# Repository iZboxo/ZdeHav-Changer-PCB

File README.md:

# ZdeHavCANdesignTCHG

> **Klipper CAN toolhead board — STM32G0B1CBT6 + TMC2209**

Custom toolhead board design for Klipper-based 3D printers. The board communicates over CAN bus and is designed for direct mounting on the print head (toolchanger or standard mount).

---

## Photos

<table>
  <tr>
    <td></td>
    <td></td>
    <td></td>
  </tr>
</table>

---

## Overview

https://izboxo.github.io/ZdeHav-Changer-PCB/bom/ibom.html

| Parameter | Value |
|---|---|
| MCU | STM32G0B1CBT6 (Cortex-M0+, 64 MHz, 128 KB Flash, LQFP-48) |
| CAN transceiver | SN65HVD230 (3.3 V, 1 Mbit/s, SOIC-8) |
| Stepper driver | TMC2209 (UART) |
| USB | USB-C (D+ / D−, DFU support) |
| Power input | 5 V via USB-C |
| Logic voltage | 3.3 V |
| Crystal | 16 MHz / 10 pF (HSE) |
| PCB | 4-layer |
| Schematic rev. | 1.0 (2026-02-02) |
| Firmware | Klipper (CANBUS UUID) |

---

## Features

- **CAN bus** — SN65HVD230, 120 Ω termination resistor (R26), slope-control resistor on RS pin
- **TMC2209** — STEP / DIR / EN / DIAG, UART via USART2 (`USART2_TX_2209_PDN`), SpreadCycle/StealthChop
- **Thermistors** — 3× ADC inputs (THERM-1, THERM-2, THERM-3)
- **Heater** — PWM output (`TIM3_HE`) for hotend heater
- **Fan** — PWM output (`TIM3_FAN`) for part cooling fan
- **NeoPixel** — 1× WS2812B-Mini (5 V), GPIO output `GPIO_NEOPIXEL`
- **Piezo buzzer** — GPIO output `GPIO_PIEZO` via dedicated subsheet
- **SWD** — SWDIO / SWCLK for debug (Black Magic Probe / J-Link)
- **BOOT0** — SPDT switch (SW1) for toggling DFU / normal boot
- **Filtered VREF** — ferrite bead (FB1) + bypass capacitor array (C1–C8) for clean analog VREF

---

## Schematic Structure

| Sheet | File | Contents |
|---|---|---|
| Main | `ZdeHavCANdesignTCHG.kicad_sch` | MCU, CAN transceiver, crystal, NeoPixel, SWD, BOOT0 |
| Power | `usbc.kicad_sch` | USB-C connector, 5 V / 3.3 V power, CAN input |
| Piezo | `piezo.kicad_sch` | Piezo buzzer and driver |
| Extruder | `extruder.kicad_sch` | TMC2209, extruder connector |
| TH+HT | `thermistorsandheaters.kicad_sch` | Thermistors (3×), heater, fan MOSFETs |

---

## Pinout MCU (key functions)

| STM32 Pin | Function |
|---|---|
| PD0 | FDCAN1_RX |
| PD1 | FDCAN1_TX |
| PA0 / PA1 | ADC1_IN0 / ADC1_IN1 (THERM-1, THERM-2) |
| PC6 | TIM3_CH1 — heater PWM |
| PC7 | TIM3_CH2 — fan PWM |
| PA13 / PA14 | SWDIO / SWCLK (SWD) |
| PA14 / BOOT0 | BOOT0 (switch SW1) |
| PF0 / PF1 | HSE IN / OUT (16 MHz crystal) |

> See schematic for full pin mapping.

---

## Firmware — Klipper

The board is intended to run as a Klipper CAN node.

Example `printer.cfg` snippet:

```ini
[mcu head0]
canbus_uuid: <YOUR_UUID_HERE>

[extruder]
step_pin: head0:PD1
dir_pin: head0:PD0
# ... fill in remaining pins per your wiring

[temperature_sensor toolhead_NTC]
sensor_type: NTC 100K MGB18-104F39050L32
sensor_pin: head0:PA0
```

---

## Manufacturing

A ready-to-order fabrication archive **`CANTCHG28.zip`** is available in the project files. This file is specifically prepared for **JLCPCB** (4-layer stackup) and contains all necessary files (Gerber, BOM, CPL) for production.

---
## Dependencies

- [KiCad 9.0](https://www.kicad.org/)
- [Klipper firmware](https://github.com/Klipper3d/klipper)

---

## License

This hardware design is released as open-source under the **MIT** license.

---

*Design: Zdeněk Havlát — [zdehav.cz](https://zdehav.cz)*

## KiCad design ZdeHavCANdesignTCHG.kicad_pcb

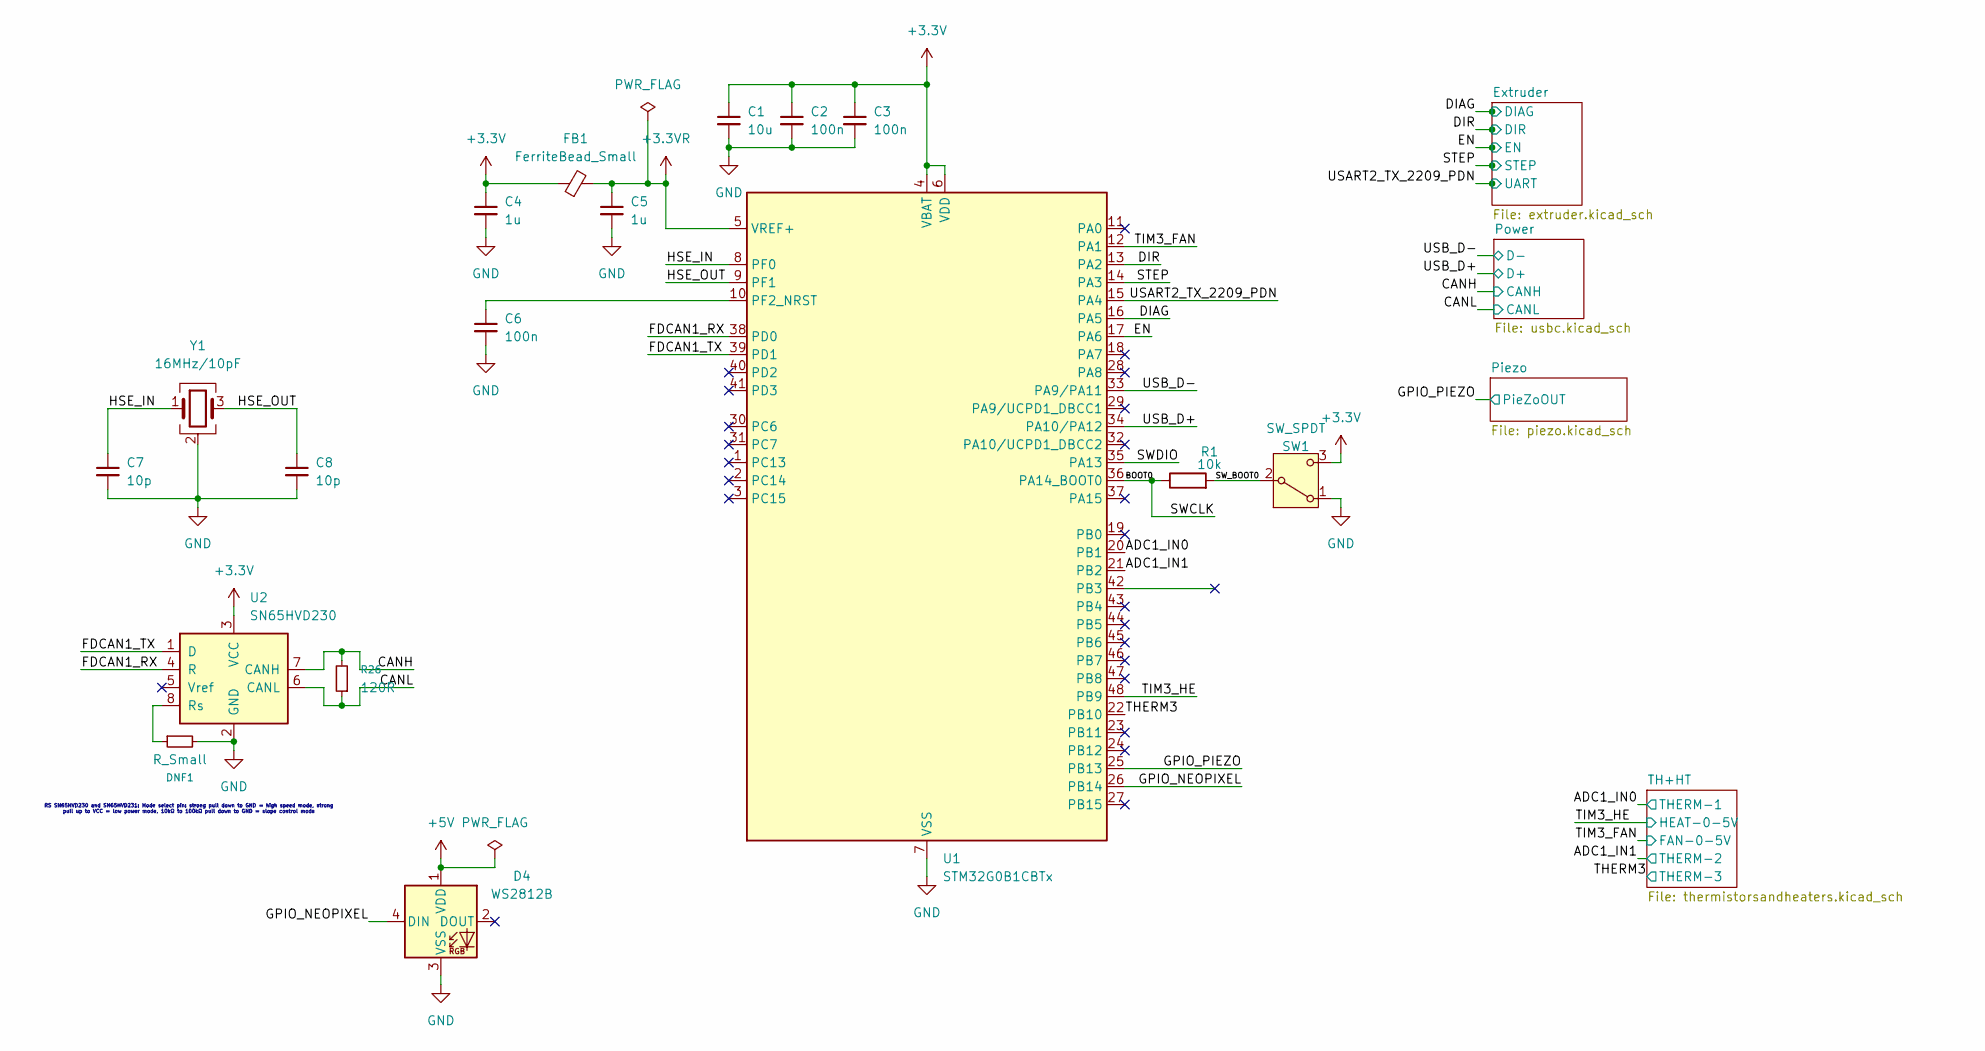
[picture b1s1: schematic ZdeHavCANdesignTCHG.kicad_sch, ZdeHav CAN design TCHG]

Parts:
C1: 10u; C_0603_1608Metric_Pad1.08x0.95mm_HandSolder
C2, C3, C6: 100n; C_0603_1608Metric_Pad1.08x0.95mm_HandSolder
C4, C5: 1u; C_0603_1608Metric_Pad1.08x0.95mm_HandSolder
C7, C8: 10p; C_0603_1608Metric_Pad1.08x0.95mm_HandSolder
D4: WS2812B; LED_WS2812B-Mini_PLCC4_3.5x3.5mm
DNF1: R_Small; R_0603_1608Metric_Pad0.98x0.95mm_HandSolder
FB1: FerriteBead_Small; L_0603_1608Metric_Pad1.05x0.95mm_HandSolder
R1: 10k; R_0603_1608Metric_Pad0.98x0.95mm_HandSolder
R26: 120R; R_0603_1608Metric_Pad0.98x0.95mm_HandSolder
SW1: SW_SPDT; PinHeader_1x03_P1.00mm_Vertical
U1: STM32G0B1CBTx; LQFP-48_7x7mm_P0.5mm
U2: SN65HVD230; SOIC-8_3.9x4.9mm_P1.27mm
Y1: 16MHz/10pF; LFXTAL071255CUTT

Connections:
+3.3V: C1.1, C2.1, C3.1, C4.1, FB1.1, SW1.3 (C), U1.4 (VBAT), U1.6 (VDD), U2.3 (VCC); also elsewhere on the board
+3.3VR: C5.1, FB1.2, U1.5 (VREF+)
+5V: D4.1 (VDD); also elsewhere on the board
/ADC1_IN0: U1.20 (PB1); also elsewhere on the board
/ADC1_IN1: U1.21 (PB2); also elsewhere on the board
/BOOT0: R1.1, U1.36 (PA14_BOOT0)
/CANH: R26.2, U2.7 (CANH); also elsewhere on the board
/CANL: R26.1, U2.6 (CANL); also elsewhere on the board
/DIAG: U1.16 (PA5); also elsewhere on the board
/DIR: U1.13 (PA2); also elsewhere on the board
/EN: U1.17 (PA6); also elsewhere on the board
/FDCAN1_RX: U1.38 (PD0), U2.4 (R)
/FDCAN1_TX: U1.39 (PD1), U2.1 (D)
/GPIO_NEOPIXEL: D4.4 (DIN), U1.26 (PB14)
/GPIO_PIEZO: U1.25 (PB13); also elsewhere on the board
/HSE_IN: C7.1, U1.8 (PF0), Y1.1
/HSE_OUT: C8.1, U1.9 (PF1), Y1.3
/STEP: U1.14 (PA3); also elsewhere on the board
/SWDIO: U1.35 (PA13)
/SW_BOOT0: R1.2, SW1.2 (B)
/THERM3: U1.22 (PB10); also elsewhere on the board
/TIM3_FAN: U1.12 (PA1); also elsewhere on the board
/TIM3_HE: U1.48 (PB9); also elsewhere on the board
/USART2_TX_2209_PDN: U1.15 (PA4); also elsewhere on the board
/USB_D+: U1.34 (PA10/PA12); also elsewhere on the board
/USB_D-: U1.33 (PA9/PA11); also elsewhere on the board
GND: C1.2, C2.2, C3.2, C4.2, C5.2, C6.2, C7.2, C8.2, D4.3 (VSS), DNF1.2, SW1.1 (A), U1.7 (VSS), U2.2 (GND), Y1.2 (G), Y1.4 (G); also elsewhere on the board
unnamed: C6.1, U1.10 (PF2_NRST)
unnamed: DNF1.1, U2.8 (Rs)

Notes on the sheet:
RS SN65HVD230 and SN65HVD231: Mode select pin: strong pull down to GND = high speed mode, strong pull up to VCC = low power mode, 10kΩ to 100kΩ pull down to GND = slope control mode

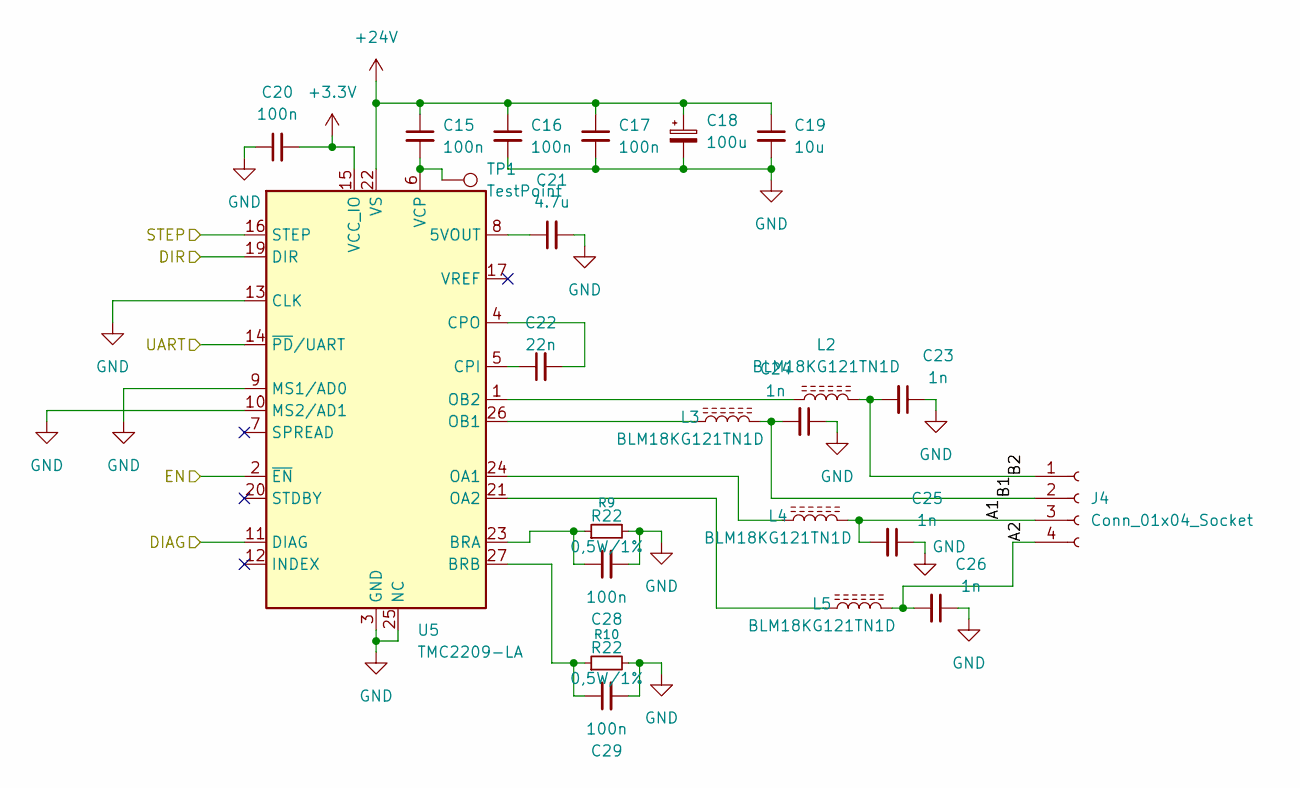
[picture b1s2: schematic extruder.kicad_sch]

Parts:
C15, C16, C17, C20, C28, C29: 100n; C_0603_1608Metric_Pad1.08x0.95mm_HandSolder
C18: 100u; C_Elec_6.3x7.7
C19: 10u; C_1206_3216Metric_Pad1.33x1.80mm_HandSolder
C21: 4.7u; C_0603_1608Metric_Pad1.08x0.95mm_HandSolder
C22: 22n; C_0603_1608Metric_Pad1.08x0.95mm_HandSolder
C23, C24, C25, C26: 1n; C_0603_1608Metric_Pad1.08x0.95mm_HandSolder
J4: Conn_01x04_Socket; JST_XH_B4B-XH-A_1x04_P2.50mm_Vertical
L2, L3, L4, L5: BLM18KG121TN1D; L_0603_1608Metric_Pad1.05x0.95mm_HandSolder
R9, R10: R22; R_1206_3216Metric_Pad1.30x1.75mm_HandSolder
TP1: TestPoint; TestPoint_Pad_D1.0mm
U5: TMC2209-LA; VQFN-28-1EP_5x5mm_P0.5mm_EP3.7x3.7mm_ThermalVias

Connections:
+3.3V: C20.2, U5.15 (VCC_IO); also elsewhere on the board
+24V: C15.1, C16.1, C17.1, C18.1, C19.1, U5.22 (VS), U5.28 (VS); also elsewhere on the board
/DIAG: U5.11 (DIAG); also elsewhere on the board
/DIR: U5.19 (DIR); also elsewhere on the board
/EN: U5.2 (~EN); also elsewhere on the board
/Extruder/A1: C25.2, J4.3, L4.2
/Extruder/A2: C26.2, J4.4, L5.2
/Extruder/B1: C24.2, J4.2, L3.2
/Extruder/B2: C23.2, J4.1, L2.2
/STEP: U5.16 (STEP); also elsewhere on the board
/USART2_TX_2209_PDN: U5.14 (~PD/UART); also elsewhere on the board
GND: C16.2, C17.2, C18.2, C19.2, C20.1, C21.2, C23.1, C24.1, C25.1, C26.1, C28.2, C29.2, R9.2, R10.2, U5.3 (GND), U5.9 (MS1/AD0), U5.10 (MS2/AD1), U5.13 (CLK), U5.18 (GND), U5.25 (NC), U5.29 (GND); also elsewhere on the board
unnamed: C21.1, U5.8 (5VOUT)
unnamed: C28.1, R9.1, U5.23 (BRA)
unnamed: C29.1, R10.1, U5.27 (BRB)
unnamed: C22.1, U5.5 (CPI)
unnamed: C22.2, U5.4 (CPO)
unnamed: L4.1, U5.24 (OA1)
unnamed: L5.1, U5.21 (OA2)
unnamed: L3.1, U5.26 (OB1)
unnamed: L2.1, U5.1 (OB2)
unnamed: C15.2, TP1.1, U5.6 (VCP)

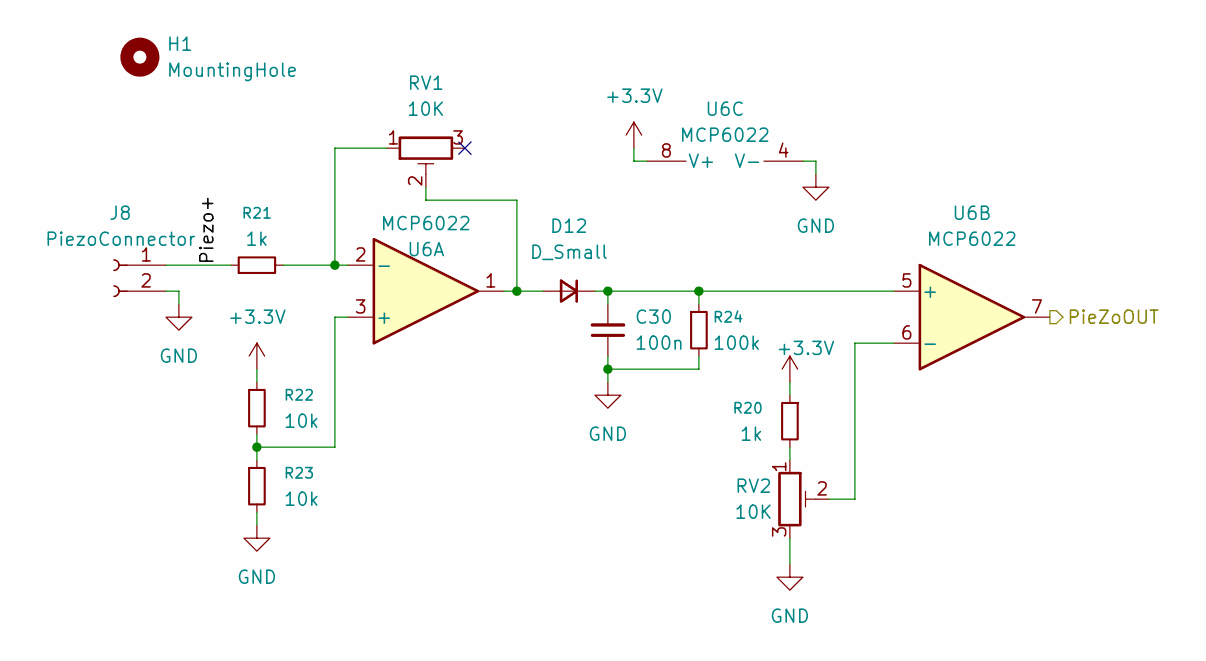
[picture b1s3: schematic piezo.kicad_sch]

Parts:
C30: 100n; C_0603_1608Metric_Pad1.08x0.95mm_HandSolder
D12: D_Small; D_0603_1608Metric_Pad1.05x0.95mm_HandSolder
H1: MountingHole; MountingHole_2.2mm_M2_Pad_Via
J8: PiezoConnector; JST_XH_B2B-XH-A_1x02_P2.50mm_Vertical
R20, R21: 1k; R_0603_1608Metric_Pad0.98x0.95mm_HandSolder
R22, R23: 10k; R_0603_1608Metric_Pad0.98x0.95mm_HandSolder
R24: 100k; R_0603_1608Metric_Pad0.98x0.95mm_HandSolder
RV1, RV2: 10K; Trimmer 10k 3305SMD
U6: MCP6022; TSSOP-8_4.4x3mm_P0.65mm

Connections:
+3.3V: R20.1, R22.1, U6.8 (V+); also elsewhere on the board
/GPIO_PIEZO: U6.7; also elsewhere on the board
/Piezo/Piezo+: J8.1, R21.1
GND: C30.1, J8.2, R23.2, R24.2, RV2.3, U6.4 (V-); also elsewhere on the board
unnamed: D12.2 (A), RV1.2, U6.1
unnamed: C30.2, D12.1 (K), R24.1, U6.5 (+)
unnamed: R20.2, RV2.1
unnamed: R22.2, R23.1, U6.3 (+)
unnamed: R21.2, RV1.1, U6.2 (-)
unnamed: RV2.2, U6.6 (-)

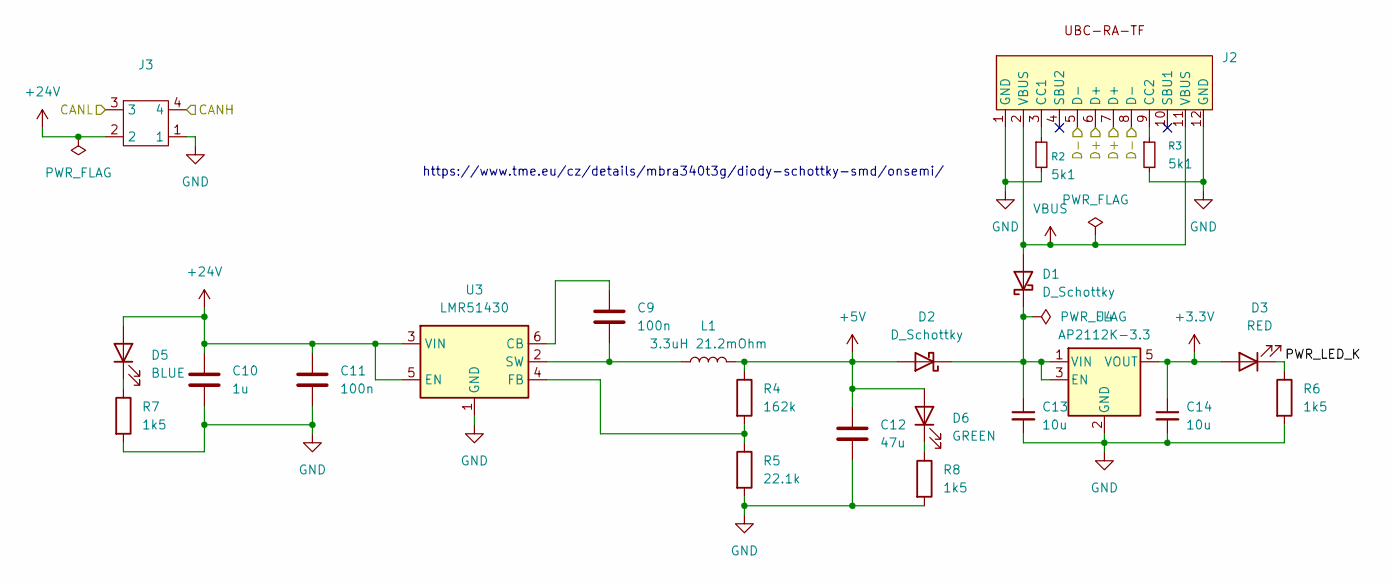
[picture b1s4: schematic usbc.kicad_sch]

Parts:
C9, C11: 100n; C_0603_1608Metric_Pad1.08x0.95mm_HandSolder
C10: 1u; C_0603_1608Metric_Pad1.08x0.95mm_HandSolder
C12: 47u; C_0603_1608Metric_Pad1.08x0.95mm_HandSolder
C13, C14: 10u; C_0603_1608Metric_Pad1.08x0.95mm_HandSolder
D1, D2: D_Schottky; D_SOD-323_HandSoldering
D3: RED; LED_0603_1608Metric_Pad1.05x0.95mm_HandSolder
D5: BLUE; LED_0603_1608Metric_Pad1.05x0.95mm_HandSolder
D6: GREEN; LED_0603_1608Metric_Pad1.05x0.95mm_HandSolder
J2: USBC
J3: Molex Micro-Fit 3.0 4
L1: 3.3uH 21.2mOhm; SD53
R2, R3: 5k1; R_0603_1608Metric_Pad0.98x0.95mm_HandSolder
R4: 162k; R_0603_1608Metric_Pad0.98x0.95mm_HandSolder
R5: 22.1k; R_0603_1608Metric_Pad0.98x0.95mm_HandSolder
R6, R7, R8: 1k5; R_0603_1608Metric_Pad0.98x0.95mm_HandSolder
U3: LMR51430; SOT-23-6
U4: AP2112K-3.3; SOT-23-5

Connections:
+3.3V: C14.1, D3.2 (A), U4.5 (VOUT); also elsewhere on the board
+5V: C12.1, D2.2 (A), D6.2 (A), L1.2, R4.1; also elsewhere on the board
+24V: C10.1, C11.1, D5.2 (A), J3.2, U3.3 (VIN), U3.5 (EN); also elsewhere on the board
/CANH: J3.4; also elsewhere on the board
/CANL: J3.3; also elsewhere on the board
/Power/PWR_LED_K: D3.1 (K), R6.1
/USB_D+: J2.6 (D+), J2.7 (D+); also elsewhere on the board
/USB_D-: J2.5 (D-), J2.8 (D-); also elsewhere on the board
GND: C10.2, C11.2, C12.2, C13.2, C14.2, J2.1 (GND), J2.12 (GND), J3.1, R2.2, R3.2, R5.2, R6.2, R7.2, R8.2, U3.1 (GND), U4.2 (GND); also elsewhere on the board
unnamed: C13.1, D1.1 (K), D2.1 (K), U4.1 (VIN), U4.3 (EN)
unnamed: D5.1 (K), R7.1
unnamed: D6.1 (K), R8.1
unnamed: J2.3 (CC1), R2.1
unnamed: J2.9 (CC2), R3.1
unnamed: C9.2, U3.6 (CB)
unnamed: R4.2, R5.1, U3.4 (FB)
unnamed: C9.1, L1.1, U3.2 (SW)
VBUS: D1.2 (A), J2.2 (VBUS), J2.11 (VBUS)

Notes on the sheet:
https://www.tme.eu/cz/details/mbra340t3g/diody-schottky-smd/onsemi/

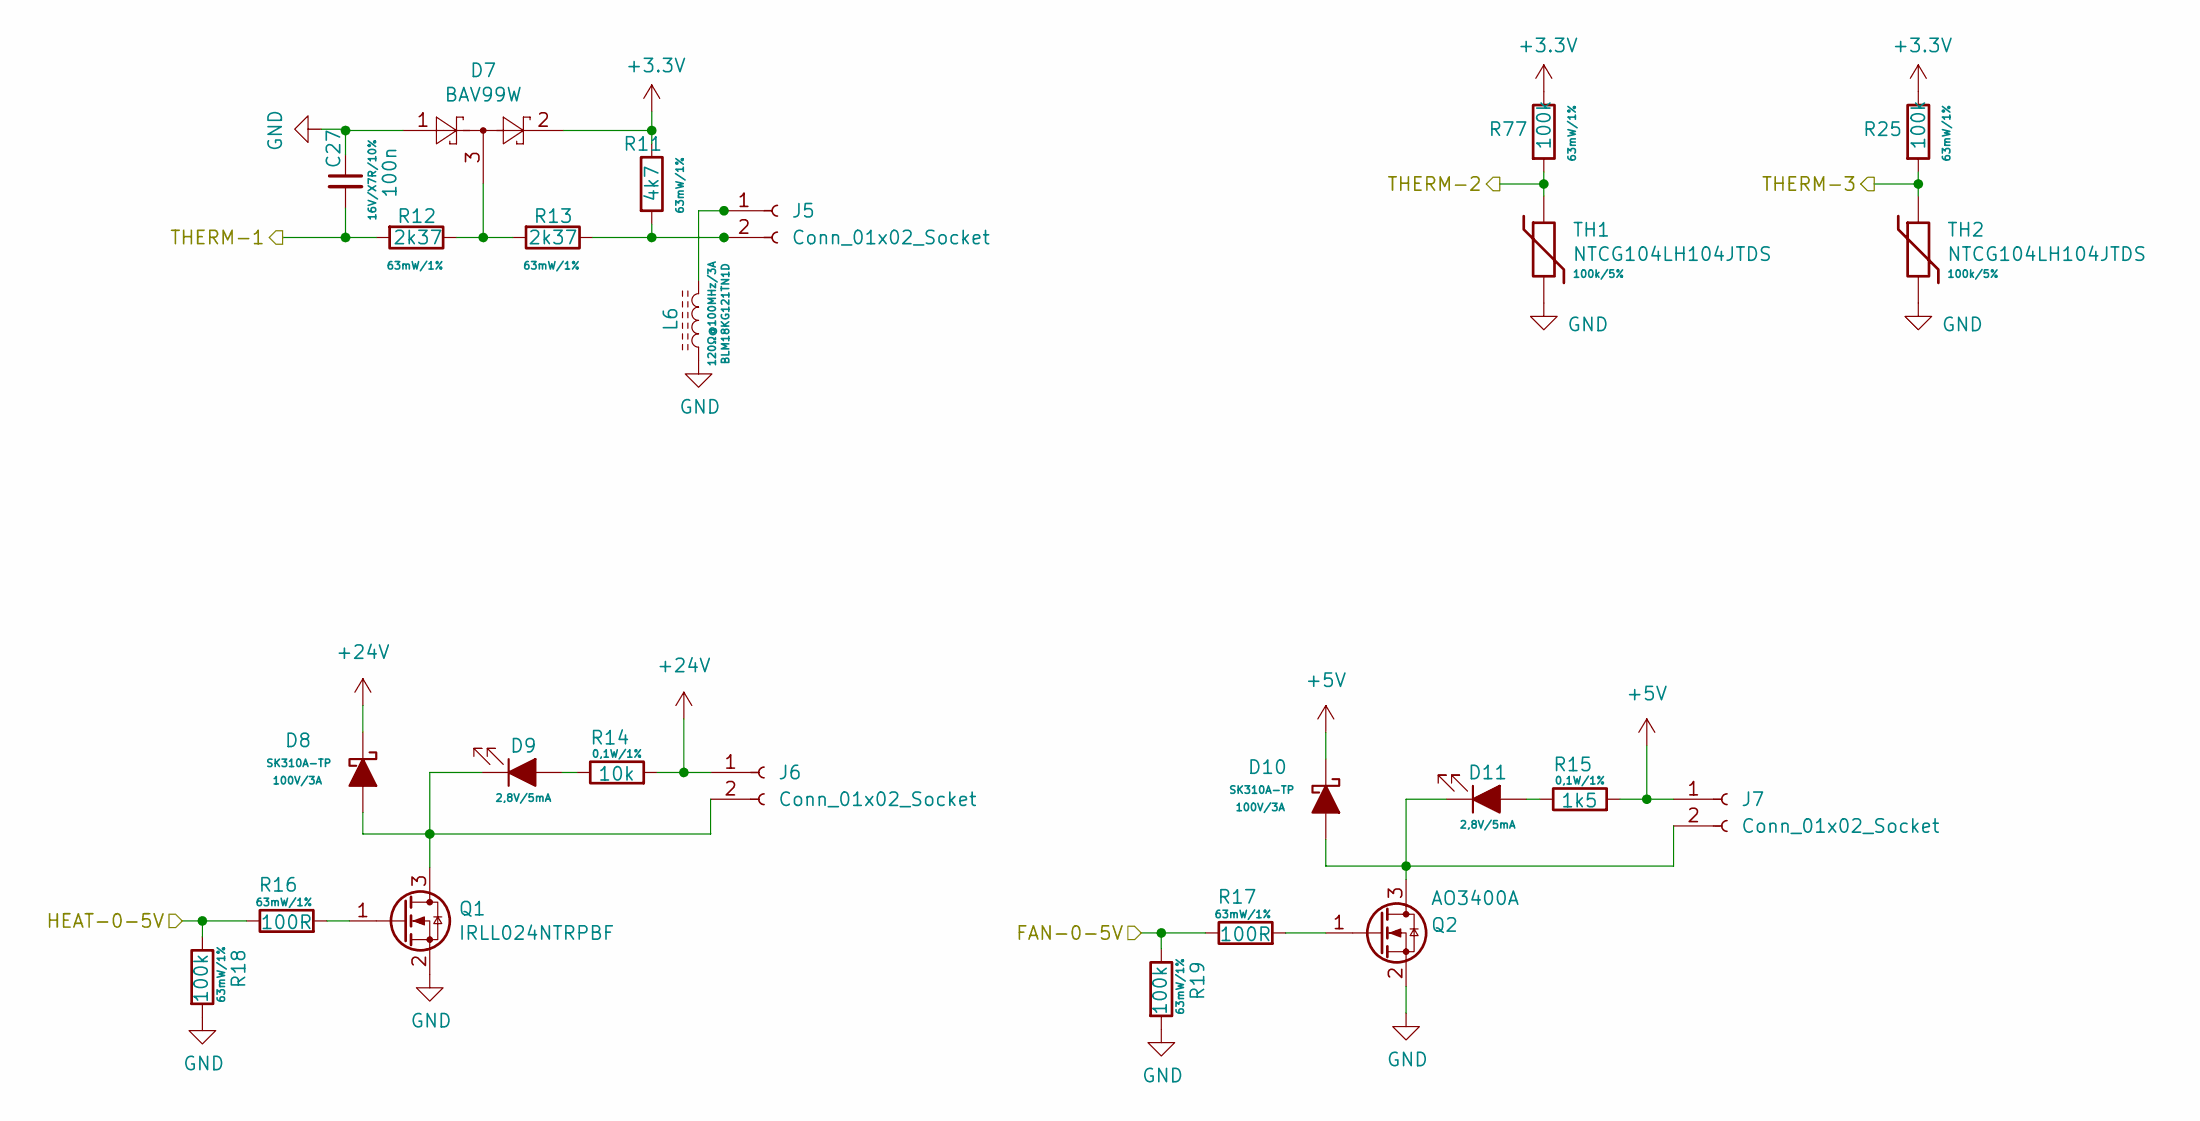
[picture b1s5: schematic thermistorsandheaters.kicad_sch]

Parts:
C27: 100n; C_0603_1608Metric_Pad1.08x0.95mm_HandSolder
D7: BAV99W; SOT-323_SC-70
D8: SK310A-TP; D_SMA
D9, D11: GRN; LED_0603_1608Metric_Pad1.05x0.95mm_HandSolder
D10: SK310A-TP; D_SOD-323_HandSoldering
J5, J6, J7: Conn_01x02_Socket; JST_XH_B2B-XH-A_1x02_P2.50mm_Vertical
L6: BLM18KG121TN1D; L_0603_1608Metric_Pad1.05x0.95mm_HandSolder
Q1: IRLL024NTRPBF; SOT-223-3_TabPin2
Q2: AO3400A; SOT-23
R11: 4k7; R_0603_1608Metric_Pad0.98x0.95mm_HandSolder
R12, R13: 2k37; R_0603_1608Metric_Pad0.98x0.95mm_HandSolder
R14: 10k; R_0603_1608Metric_Pad0.98x0.95mm_HandSolder
R15: 1k5; R_0603_1608Metric_Pad0.98x0.95mm_HandSolder
R16, R17: 100R; R_0603_1608Metric_Pad0.98x0.95mm_HandSolder
R18, R19, R25, R77: 100k; R_0603_1608Metric_Pad0.98x0.95mm_HandSolder
TH1, TH2: NTCG104LH104JTDS; R_0603_1608Metric_Pad0.98x0.95mm_HandSolder

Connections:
+3.3V: D7.2, R11.1, R25.1, R77.1; also elsewhere on the board
+5V: D10.1 (K), J7.1, R15.2; also elsewhere on the board
+24V: D8.1 (K), J6.1, R14.2; also elsewhere on the board
/ADC1_IN0: C27.2, R12.2; also elsewhere on the board
/ADC1_IN1: R77.2, TH1.1; also elsewhere on the board
/THERM3: R25.2, TH2.1; also elsewhere on the board
/TIM3_FAN: R17.1, R19.1; also elsewhere on the board
/TIM3_HE: R16.1, R18.1; also elsewhere on the board
GND: C27.1, D7.1, L6.1, Q1.2 (S), Q2.2 (S), R18.2, R19.2, TH1.2, TH2.2; also elsewhere on the board
unnamed: D7.3, R12.1, R13.2
unnamed: D8.2 (A), D9.1 (K), J6.2, Q1.3 (D)
unnamed: D9.2 (A), R14.1
unnamed: D10.2 (A), D11.1 (K), J7.2, Q2.3 (D)
unnamed: D11.2 (A), R15.1
unnamed: J5.1, L6.2
unnamed: J5.2, R11.2, R13.1
unnamed: Q1.1 (G), R16.2
unnamed: Q2.1 (G), R17.2

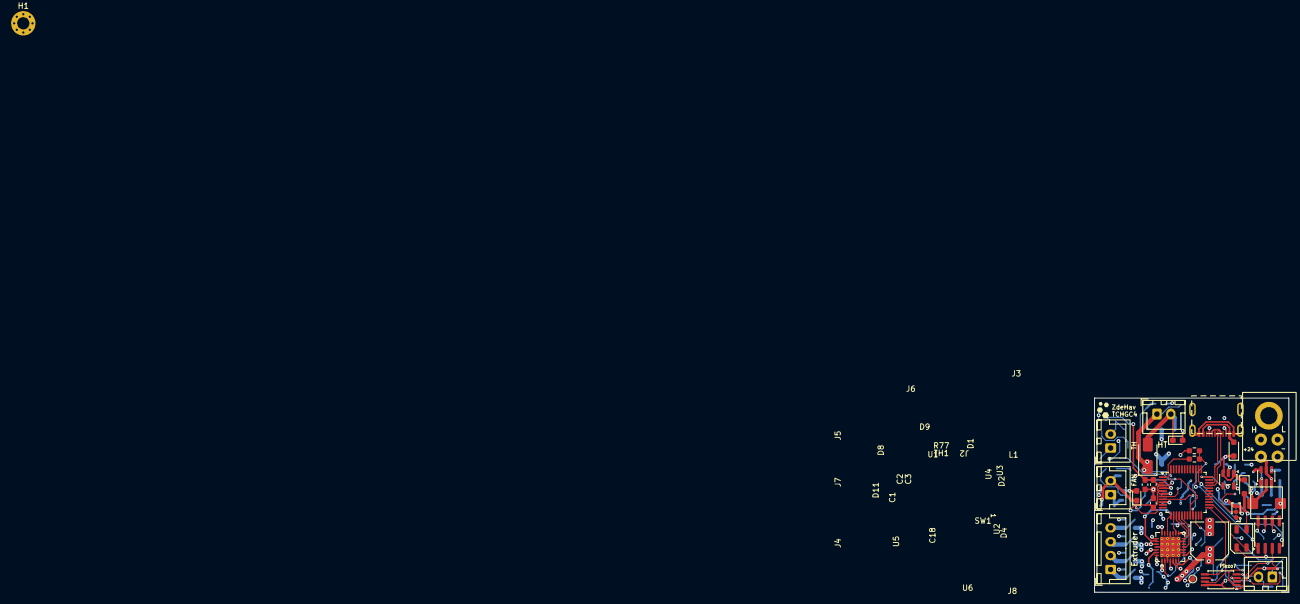
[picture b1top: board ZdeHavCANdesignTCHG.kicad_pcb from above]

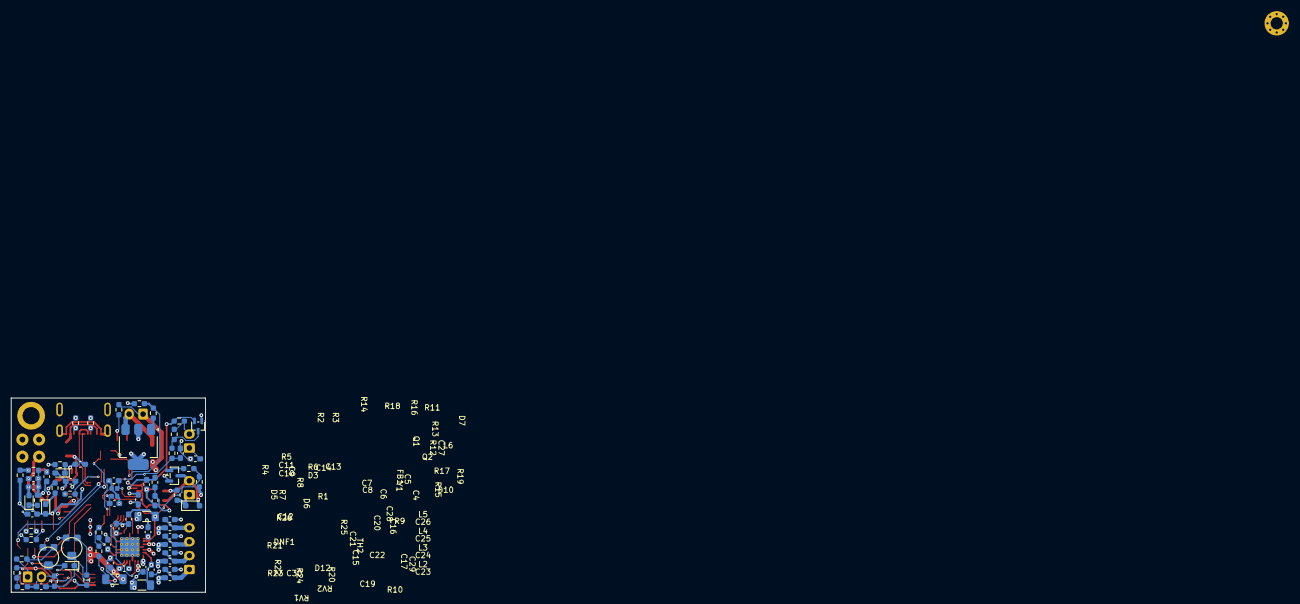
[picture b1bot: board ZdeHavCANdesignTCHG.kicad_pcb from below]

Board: 4 copper layers, 35.0 x 35.0 mm, 100 parts (71 on the bottom side), 69 nets.
